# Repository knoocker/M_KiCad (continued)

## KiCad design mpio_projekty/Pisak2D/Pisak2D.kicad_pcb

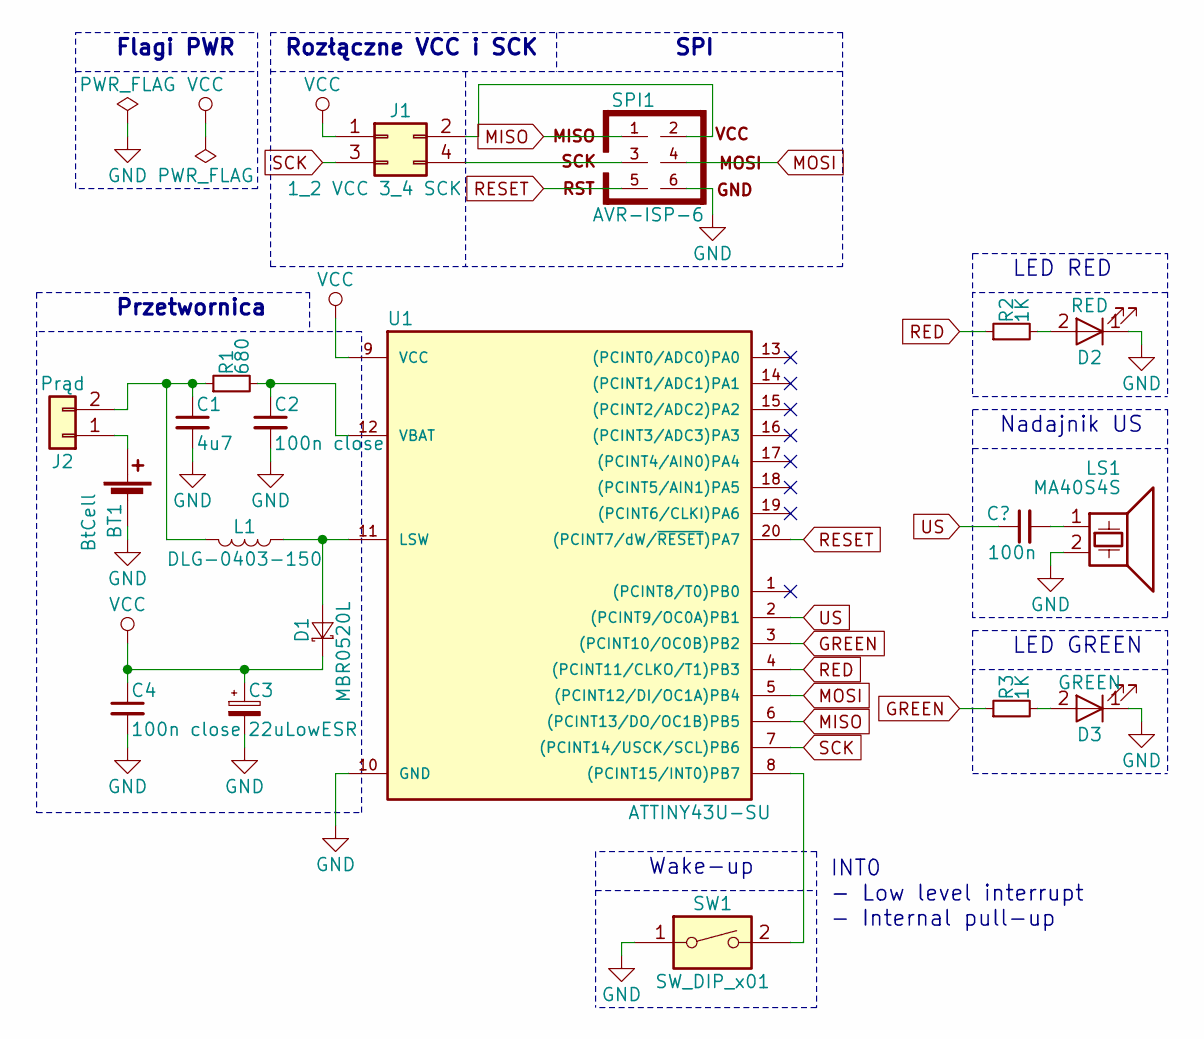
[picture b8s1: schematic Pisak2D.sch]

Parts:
BT1: BtCell; Holder_AAA
C1: 4u7; C_0603
C2, C4: 100n close; C_0603
C3: 22uLowESR; CP_Elec_5x5.3
D1: MBR0520L; D_SOD-123
D2: RED; R_0603
D3: GREEN; R_0603
J1: 1_2 VCC 3_4 SCK; Pin_Header_Straight_2x02_Pitch2.54mm
J2: Prąd; Pin_Header_Straight_1x02_Pitch2.54mm
L1: DLG-0403-150; L_0403
LS1: MA40S4S; MA40S4S_short
R1: 680; R_0603
R2, R3: 1K; R_0603
SPI1: AVR-ISP-6; Pin_Header_Straight_2x03_Pitch2.54mm
SW1: SW_DIP_x01; SW_Tactile_SPST_Angled_PTS645Vx83-2LFS
U1: ATTINY43U-SU; SOIC-20W_7.5x12.8mm_Pitch1.27mm

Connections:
GND: BT1.2 (-), C1.2, C2.2, C3.2, C4.2, D2.1 (K), D3.1 (K), LS1.2, SPI1.6, SW1.1, U1.10 (GND)
GREEN: R3.1, U1.3 ((PCINT10/OC0B)PB2)
MISO: SPI1.1, U1.6 ((PCINT13/DO/OC1B)PB5)
MOSI: SPI1.4, U1.5 ((PCINT12/DI/OC1A)PB4)
unnamed: BT1.1 (+), J2.1
unnamed: C1.1, J2.2, L1.2, R1.1
unnamed: C2.1, R1.2, U1.12 (VBAT)
unnamed: D1.2 (A), L1.1, U1.11 (LSW)
unnamed: D2.2 (A), R2.2
unnamed: D3.2 (A), R3.2
unnamed: J1.2, SPI1.2
unnamed: J1.4, SPI1.3
unnamed: SW1.2, U1.8 ((PCINT15/INT0)PB7)
RED: R2.1, U1.4 ((PCINT11/CLKO/T1)PB3)
RESET: SPI1.5, U1.20 ((PCINT7/dW/~RESET~)PA7)
SCK: J1.3, U1.7 ((PCINT14/USCK/SCL)PB6)
US: LS1.1, U1.2 ((PCINT9/OC0A)PB1)
VCC: C3.1, C4.1, D1.1 (K), J1.1, U1.9 (VCC)

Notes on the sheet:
SPI
Rozłączne VCC i SCK
Przetwornica
Flagi PWR
INT0 - Low level interrupt - Internal pull-up
Wake-up
Nadajnik US
LED RED
LED GREEN

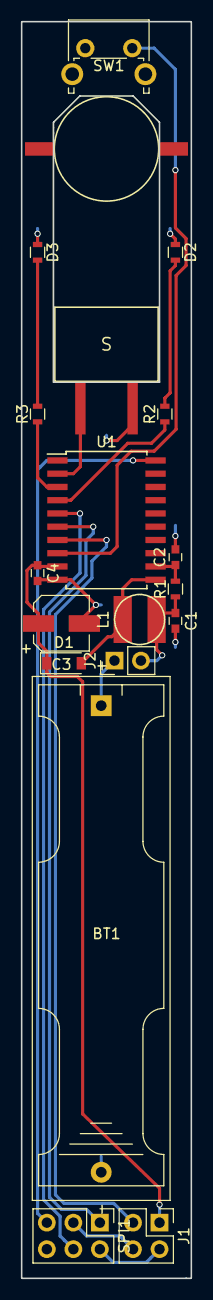
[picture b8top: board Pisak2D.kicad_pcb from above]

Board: 2 copper layers, 16.3 x 120.4 mm, 18 parts (0 on the bottom side), 18 nets.

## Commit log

2018-05-28 KiCad
2018-05-30 resetUSBv4.8
2018-06-01 resetUSBv4.9 radiator w środku obudowy
2018-06-01 resetUSBradWewnatrz,Zewnatrz, AGND bez przelotek.
2018-06-01 resetUSB zmienione płytki radiator wewnętrzny i zewnętrzny
2018-06-04 resetUSBv4.92radWew
2018-06-25 resetUSBv4.95stabilizator
2018-06-25 stabilizator
2018-06-28 resetusb pdf
2018-07-03 resetUSBv4.98com2
2018-07-03 resetUSB4.98
2018-07-19 pisakUS
2018-07-24 KnoockerV2
